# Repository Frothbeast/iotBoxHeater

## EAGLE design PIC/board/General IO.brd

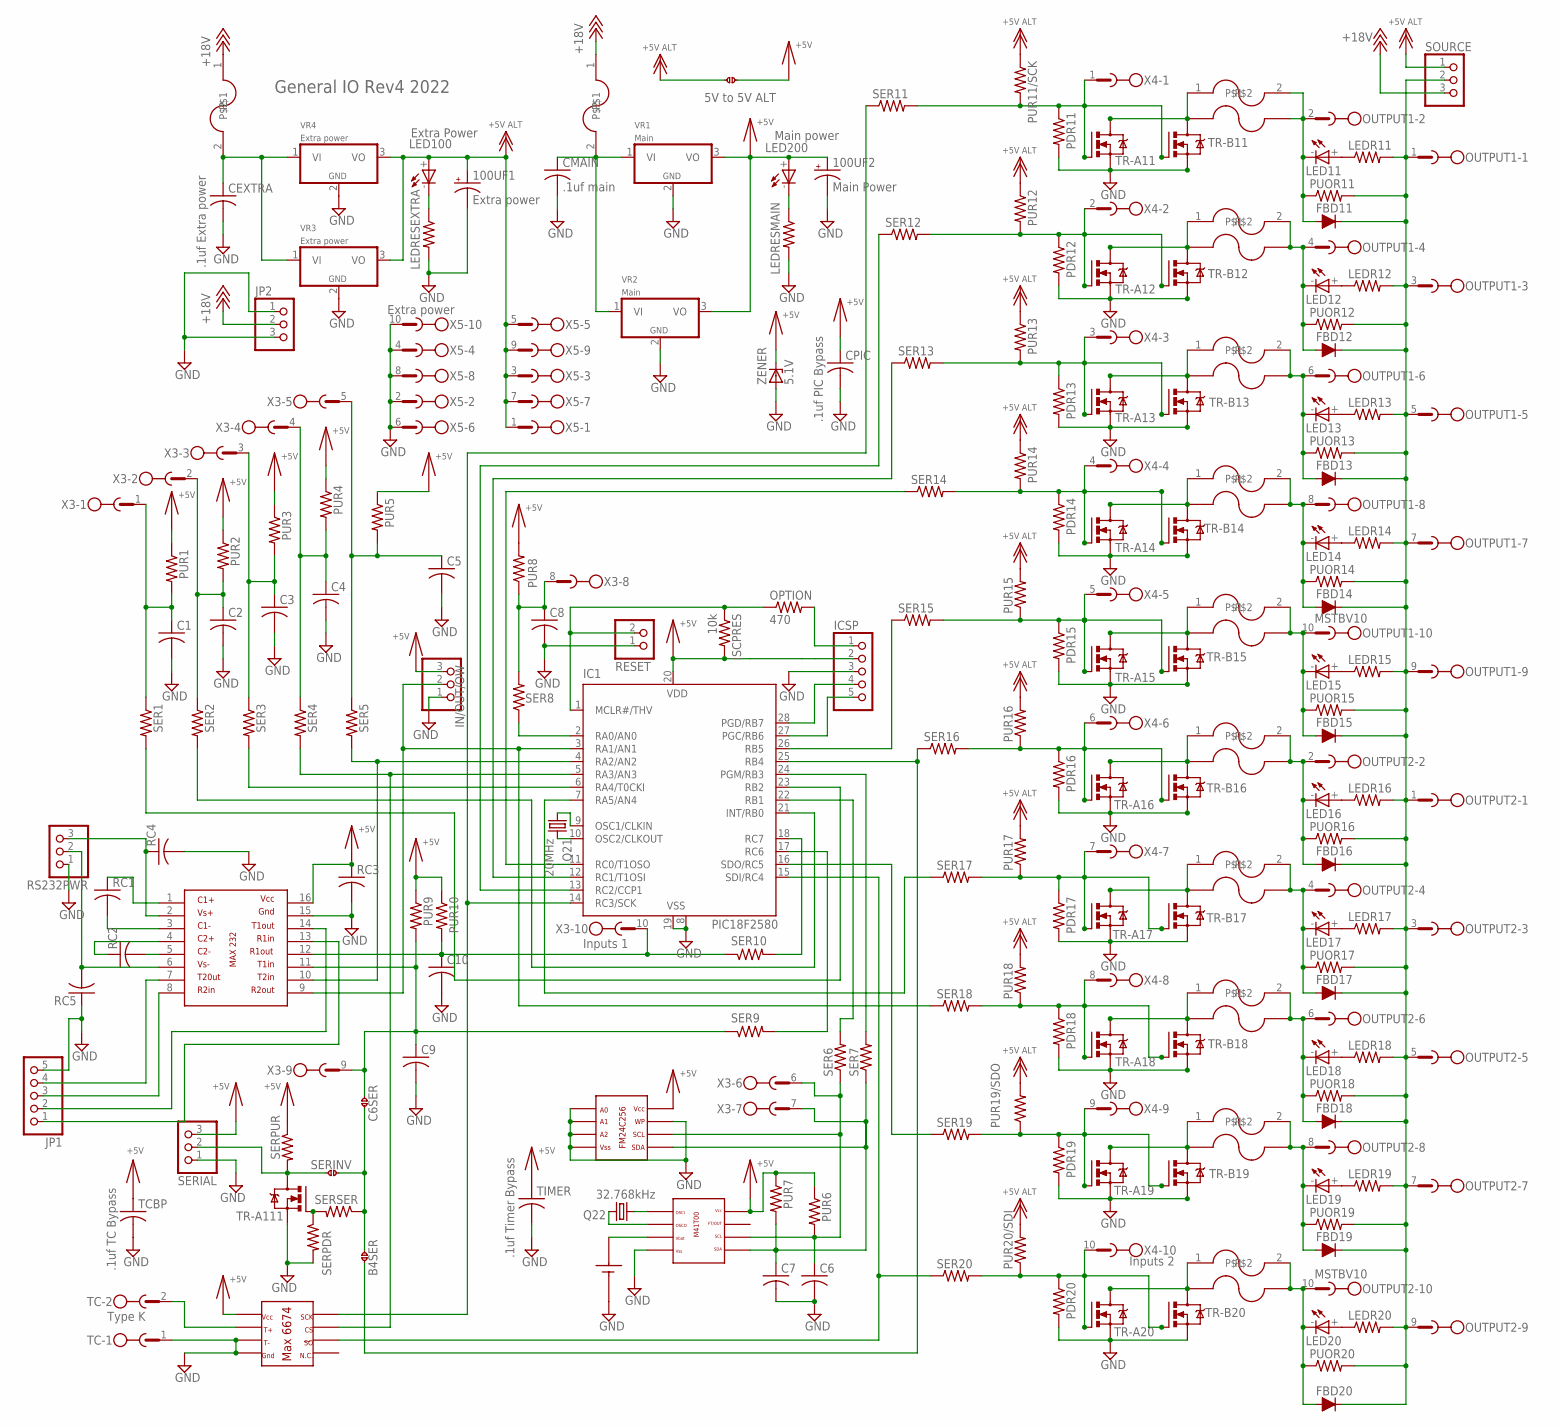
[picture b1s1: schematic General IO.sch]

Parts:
100UF1: Extra power; PANASONIC_G
100UF2: Main Power; PANASONIC_G
BAT1: BH-401
C1, C2, C3, C4, C5, C6, C7, C8, C9, C10: CAPACITOR-NO-POLARITYC1210; C1210
C6SER: SPLIT_PAD
CEXTRA: .1uf Extra power; C1210
CMAIN: .1uf main; C1210
CPIC: .1uf PIC Bypass; C1210
FBD11, FBD12, FBD13, FBD14, FBD15, FBD16, FBD17, FBD18, FBD19, FBD20: D-FILL-SOD-87; SOD87
FUSE9, FUSE11, FUSE12, FUSE13, FUSE14, FUSE15, FUSE16, FUSE17, FUSE18, FUSE20: FUSE(SM); FUSE
IC1: PIC18F2580; SO-28W
ICSP: PINHD-1X5; 1X05
IN/OUT/OW: PINHD-1X3; 1X03
ISCPRES: 10k; M1406
JP1: PINHD-1X5; 1X05
JP2: PINHD-1X3; 1X03
LED11, LED12, LED13, LED14, LED15, LED16, LED17, LED18, LED19, LED20: LED; 1206
LED100: Extra Power; 1206
LED200: Main power; 1206
LEDR11, LEDR12, LEDR13, LEDR14, LEDR15, LEDR16, LEDR17, LEDR18, LEDR19, LEDR20: RESISITORM1406; M1406
LEDRESEXTRA: RESISITORR1210; R1210
LEDRESMAIN: RESISITORR1210; R1210
OPTION: 470; M1406
OUTPUT1, OUTPUT2: MSTBV10
PDR11, PDR12, PDR13, PDR14, PDR15, PDR16, PDR17, PDR18, PDR19, PDR20: RESISITORM1406; M1406
POLYFUSE11, POLYFUSE12, POLYFUSE13, POLYFUSE14, POLYFUSE15, POLYFUSE16, POLYFUSE17, POLYFUSE18, POLYFUSE19, POLYFUSE20: POLYFUSE; 0204/5
POLYFUSE100: Extra Power; 0204/5
POLYFUSE200: Main power; 0204/5
PUOR11, PUOR12, PUOR13, PUOR14, PUOR15, PUOR16, PUOR17, PUOR18, PUOR19, PUOR20: RESISITORM1406; M1406
PUR1, PUR2, PUR3, PUR4, PUR5, PUR6, PUR7, PUR8, PUR9, PUR10, PUR11/SCK, PUR12, PUR13, PUR14, PUR15, PUR16, PUR17, PUR18, PUR19/SDO, PUR20/SDI: RESISITORM1406; M1406
Q21: 20MHz; SM49
Q22: 32.768kHz; TC26H
RC1, RC2, RC3, RC4, RC5: CAPACITOR-NO-POLARITYC1210; C1210
RESET: PINHD-1X2; 1X02
RS232PWR: PINHD-1X3; 1X03
SER1, SER2, SER3, SER4, SER5, SER6, SER7, SER8, SER9, SER10, SER11, SER12, SER13, SER14, SER15, SER16, SER17, SER18, SER19, SER20: RESISITORM1406; M1406
SERIAL: PINHD-1X3; 1X03
SERPDR: RESISITORM1406; M1406
SERPUR: RESISITORM1406; M1406
SERSER: RESISITORM1406; M1406
SOURCE: PINHD-1X3; 1X03
TC: Type K; MSTBV2
TCBP: .1uf TC Bypass; C1210
TIMER: .1uf Timer Bypass; C1210
TR-A11, TR-A12, TR-A13, TR-A14, TR-A15, TR-A16, TR-A17, TR-A18, TR-A19, TR-A20, TR-A111: ZXMN10A08GSOT223; SOT223R_INFINEON
TR-B11, TR-B12, TR-B13, TR-B14, TR-B15, TR-B16, TR-B17, TR-B18, TR-B19, TR-B20: ZXMN10A08G; TO220BV
U$1: MAX232; SO16
U$2: MAX6674; SO08
U$4: M41T00TIMER-I2C; SO08
U$18: FM24C256; SO08
U$21, U$23, U$24: SPLIT_PAD
VR1: Main; TO220S
VR2: Main; SOT223R_INFINEON
VR3: Extra power; SOT223R_INFINEON
VR4: Extra power; TO220S
X3: Inputs 1; MSTBV10
X4: Inputs 2; MSTBV10
X5: Extra power; MSTBV10
ZENER: 5.1V; SMB

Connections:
$N199: IC1.15 (SDI/RC4), SER20.1, U$2.7
+5V: 100UF2.+, CPIC.1, IC1.20 (VDD), ICSP.2, IN/OUT/OW.3, ISCPRES.2, LED200.+, PUR1.1, PUR2.1, PUR3.1, PUR4.1, PUR5.1, PUR6.1, PUR7.1, PUR8.2, PUR9.1, PUR10.1, RC3.1, SERIAL.3, SERPUR.1, TCBP.1, TIMER.1, U$1.16, U$2.4, U$4.8 (VCC), U$18.8 (VDD), U$21.P$1, VR1.3 (VO), VR2.3 (VO), ZENER.C
+18V: JP2.2, POLYFUSE100.1, POLYFUSE200.1, SOURCE.3
ALT5V: 100UF1.+, LED100.+, PUR11/SCK.1, PUR12.1, PUR13.1, PUR14.1, PUR15.2, PUR16.2, PUR17.2, PUR18.2, PUR19/SDO.2, PUR20/SDI.2, SOURCE.1, U$21.P$2, VR3.3 (VO), VR4.3 (VO), X5.1, X5.3, X5.5, X5.7, X5.9
GND: 100UF1.-, 100UF2.-, BAT1.P$2, C1.2, C2.2, C3.2, C4.2, C5.2, C6.2, C7.2, C8.2, C9.2, C10.2, CEXTRA.2, CMAIN.2, CPIC.2, IC1.8 (VSS), IC1.19 (VSS), ICSP.3, IN/OUT/OW.1, JP1.5, JP2.1, JP2.3, LEDRESEXTRA.2, LEDRESMAIN.2, PDR11.2, PDR12.2, PDR13.2, PDR14.2, PDR15.2, PDR16.2, PDR17.2, PDR18.2, PDR19.2, PDR20.2, RC3.2, RC4.2, RC5.1, RESET.1, RS232PWR.1, SERIAL.1, SERPDR.2, TC.1, TCBP.2, TIMER.2, TR-A11.3 (S), TR-A12.3 (S), TR-A13.3 (S), TR-A14.3 (S), TR-A15.3 (S), TR-A16.3 (S), TR-A17.3 (S), TR-A18.3 (S), TR-A19.3 (S), TR-A20.3 (S), TR-A111.3 (S), TR-B11.S, TR-B12.S, TR-B13.S, TR-B14.S, TR-B15.S, TR-B16.S, TR-B17.S, TR-B18.S, TR-B19.S, TR-B20.S, U$1.15, U$2.1, U$2.2, U$4.4 (VSS), U$18.1 (A0), U$18.2 (A1), U$18.3 (A2), U$18.4 (VSS), U$18.7 (WP), VR1.2 (GND), VR2.2 (GND), VR3.2 (GND), VR4.2 (GND), X5.2, X5.4, X5.6, X5.8, X5.10, ZENER.A
unnamed: FUSE17.P$1, POLYFUSE17.1, TR-A17.2 (D), TR-B17.D
unnamed: FUSE9.P$1, POLYFUSE19.1, TR-A19.2 (D), TR-B19.D
unnamed: PDR18.1, PUR18.1, SER18.2, TR-A18.1 (G), TR-B18.G, X4.8
unnamed: FBD16.2 (A), FUSE16.P$2, LED16.-, OUTPUT2.2, POLYFUSE16.2, PUOR16.1
unnamed: FBD17.2 (A), FUSE17.P$2, LED17.-, OUTPUT2.4, POLYFUSE17.2, PUOR17.1
unnamed: FUSE16.P$1, POLYFUSE16.1, TR-A16.2 (D), TR-B16.D
unnamed: FUSE18.P$1, POLYFUSE18.1, TR-A18.2 (D), TR-B18.D
unnamed: IC1.7 (RA5/AN4), SER17.1
unnamed: FBD20.2 (A), FUSE20.P$2, LED20.-, OUTPUT2.10, POLYFUSE20.2, PUOR20.1
unnamed: FBD18.2 (A), FUSE18.P$2, LED18.-, OUTPUT2.6, POLYFUSE18.2, PUOR18.1
unnamed: IC1.16 (SDO/RC5), SER19.1
unnamed: IC1.2 (RA0/AN0), SER8.1
unnamed: FBD19.2 (A), FUSE9.P$2, LED19.-, OUTPUT2.8, POLYFUSE19.2, PUOR19.1
unnamed: FUSE20.P$1, POLYFUSE20.1, TR-A20.2 (D), TR-B20.D
unnamed: IC1.21 (INT/RB0), SER2.2
unnamed: FBD12.2 (A), FUSE12.P$2, LED12.-, OUTPUT1.4, POLYFUSE12.2, PUOR12.1
unnamed: FUSE15.P$1, POLYFUSE15.1, TR-A15.2 (D), TR-B15.D
unnamed: FBD15.2 (A), FUSE15.P$2, LED15.-, OUTPUT1.10, POLYFUSE15.2, PUOR15.1
unnamed: JP1.4, U$1.7
unnamed: PDR17.1, PUR17.1, SER17.2, TR-A17.1 (G), TR-B17.G, X4.7
unnamed: FUSE14.P$1, POLYFUSE14.1, TR-A14.2 (D), TR-B14.D
unnamed: FBD14.2 (A), FUSE14.P$2, LED14.-, OUTPUT1.8, POLYFUSE14.2, PUOR14.1
unnamed: FUSE13.P$1, POLYFUSE13.1, TR-A13.2 (D), TR-B13.D
unnamed: FBD13.2 (A), FUSE13.P$2, LED13.-, OUTPUT1.6, POLYFUSE13.2, PUOR13.1
unnamed: PDR15.1, PUR15.1, SER15.2, TR-A15.1 (G), TR-B15.G, X4.5
unnamed: PDR13.1, PUR13.2, SER13.2, TR-A13.1 (G), TR-B13.G, X4.3
unnamed: FUSE12.P$1, POLYFUSE12.1, TR-A12.2 (D), TR-B12.D
unnamed: PDR14.1, PUR14.2, SER14.2, TR-A14.1 (G), TR-B14.G, X4.4
unnamed: FUSE11.P$1, POLYFUSE11.1, TR-A11.2 (D), TR-B11.D
unnamed: FBD11.2 (A), FUSE11.P$2, LED11.-, OUTPUT1.2, POLYFUSE11.2, PUOR11.1
unnamed: IC1.28 (PGD/RB7), ICSP.4
unnamed: PDR16.1, PUR16.1, SER16.2, TR-A16.1 (G), TR-B16.G, X4.6
unnamed: IC1.23 (RB2), SER1.2
unnamed: ICSP.1, OPTION.2
unnamed: IC1.10 (OSC2/CLKOUT), Q21.2
unnamed: SERPDR.1, SERSER.2, TR-A111.1 (G)
unnamed: IC1.1 (MCLR#/THV), ISCPRES.1, OPTION.1, RESET.2
unnamed: SERIAL.2, SERPUR.2, TR-A111.2 (D), U$23.P$1
unnamed: IC1.9 (OSC1/CLKIN), Q21.1
unnamed: IC1.27 (PGC/RB6), ICSP.5
unnamed: C10.1, PUR10.2, SER10.1, U$1.12, X3.10
unnamed: IC1.4 (RA2/AN2), SER5.2, U$1.10
unnamed: C6SER.P$1, C9.1, PUR9.2, SER9.1, U$1.11, X3.9
unnamed: JP1.3, U$1.8
unnamed: TC.2, U$2.3
unnamed: CEXTRA.1, POLYFUSE100.2, VR3.1 (VI), VR4.1 (VI)
unnamed: C2.1, PUR2.2, SER2.1, X3.2
unnamed: JP1.2, U$1.14
unnamed: C4.1, PUR4.2, SER4.1, X3.4
unnamed: FBD11.1 (C), FBD12.1 (C), FBD13.1 (C), FBD14.1 (C), FBD15.1 (C), FBD16.1 (C), FBD17.1 (C), FBD18.1 (C), FBD19.1 (C), FBD20.1 (C), LEDR11.2, LEDR12.2, LEDR13.2, LEDR14.2, LEDR15.2, LEDR16.2, LEDR17.2, LEDR18.2, LEDR19.2, LEDR20.2, OUTPUT1.1, OUTPUT1.3, OUTPUT1.5, OUTPUT1.7, OUTPUT1.9, OUTPUT2.1, OUTPUT2.3, OUTPUT2.5, OUTPUT2.7, OUTPUT2.9, PUOR11.2, PUOR12.2, PUOR13.2, PUOR14.2, PUOR15.2, PUOR16.2, PUOR17.2, PUOR18.2, PUOR19.2, PUOR20.2, SOURCE.2
unnamed: Q22.1, U$4.2 (OSCO)
unnamed: Q22.2, U$4.1 (OSCI)
unnamed: LED200.-, LEDRESMAIN.1
unnamed: BAT1.P$1, U$4.3 (VBAT)
unnamed: IC1.22 (RB1), SER6.2
unnamed: PDR11.1, PUR11/SCK.2, SER11.2, TR-A11.1 (G), TR-B11.G, X4.1
unnamed: IC1.24 (PGM/RB3), SER7.2
unnamed: JP1.1, U$1.13
unnamed: C8.1, PUR8.1, SER8.2, X3.8
unnamed: IC1.18 (RC7), SER10.2
unnamed: CMAIN.1, POLYFUSE200.2, VR1.1 (VI), VR2.1 (VI)
unnamed: LED20.+, LEDR20.1
unnamed: LED19.+, LEDR19.1
unnamed: LED100.-, LEDRESEXTRA.1
unnamed: LED18.+, LEDR18.1
unnamed: IC1.17 (RC6), SER9.2
unnamed: LED17.+, LEDR17.1
unnamed: LED16.+, LEDR16.1
unnamed: LED15.+, LEDR15.1
unnamed: LED14.+, LEDR14.1
unnamed: LED13.+, LEDR13.1
unnamed: LED12.+, LEDR12.1
unnamed: LED11.+, LEDR11.1
unnamed: PDR12.1, PUR12.2, SER12.2, TR-A12.1 (G), TR-B12.G, X4.2
unnamed: C3.1, PUR3.2, SER3.1, X3.3
unnamed: PDR19.1, PUR19/SDO.1, SER19.2, TR-A19.1 (G), TR-B19.G, X4.9
unnamed: PDR20.1, PUR20/SDI.1, SER20.2, TR-A20.1 (G), TR-B20.G, X4.10
unnamed: RC2.2, U$1.5
unnamed: RC1.2, U$1.3
unnamed: RC2.1, U$1.4
unnamed: RC1.1, U$1.1
unnamed: RC4.1, RS232PWR.3, U$1.2
unnamed: RC5.2, RS232PWR.2, U$1.6
unnamed: C5.1, PUR5.2, SER5.1, X3.5
unnamed: C1.1, PUR1.2, SER1.1, X3.1
unnamed: IC1.14 (RC3/SCK), SER11.1, U$2.5
unnamed: IC1.13 (RC2/CCP1), SER12.1
unnamed: IC1.12 (RC1/T1OSI), SER13.1
unnamed: IC1.5 (RA3/AN3), SER4.2, U$2.6
unnamed: IC1.6 (RA4/T0CKI), SER3.2
unnamed: IC1.11 (RC0/T1OSO), SER14.1
unnamed: IC1.25 (RB4), SER16.1, U$24.P$2
unnamed: IC1.26 (RB5), SER15.1
unnamed: C6SER.P$2, SERSER.1, U$23.P$2, U$24.P$1
unnamed: C6.1, PUR6.2, SER6.1, U$4.6 (SCL), U$18.6 (SCL), X3.6
unnamed: C7.1, PUR7.2, SER7.1, U$4.5 (SDA), U$18.5 (SDA), X3.7
SER18: IC1.3 (RA1/AN1), IN/OUT/OW.2, SER18.1, U$1.9

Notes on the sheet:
General IO Rev4 2022
C6SER
B4SER
SERINV
5V to 5V ALT

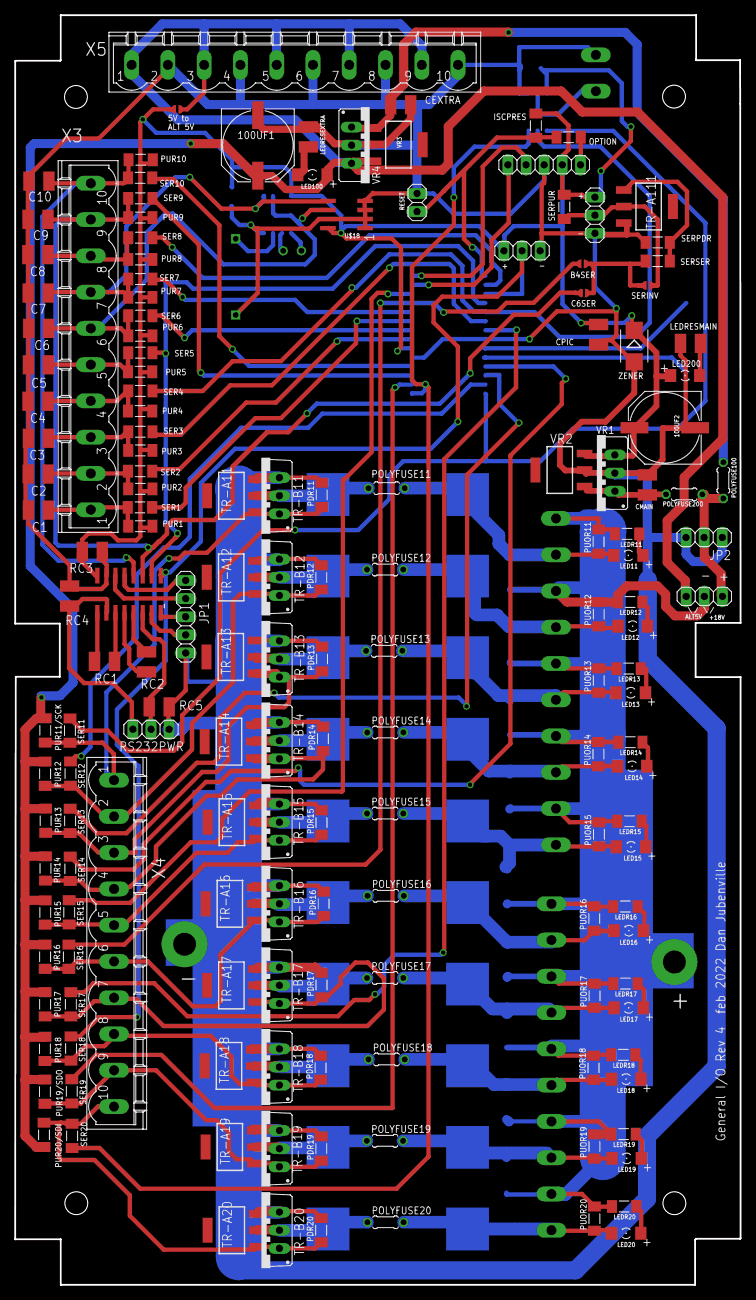
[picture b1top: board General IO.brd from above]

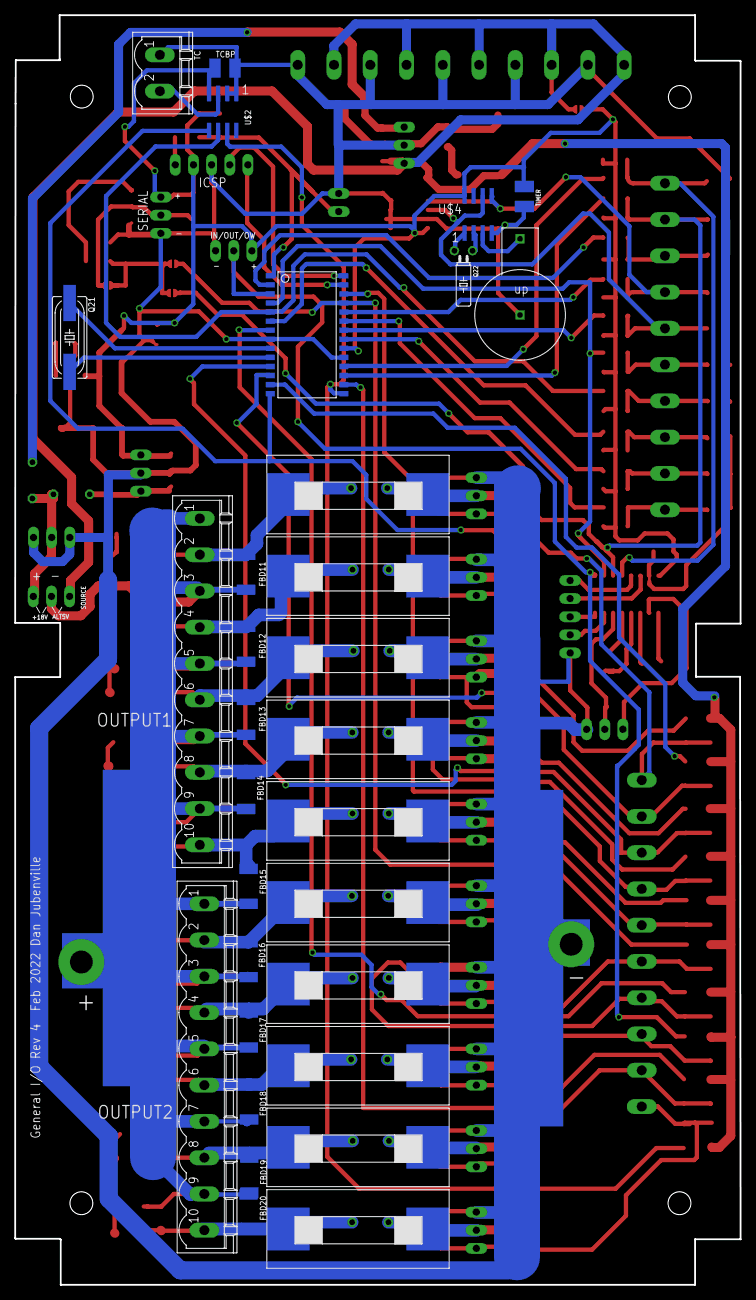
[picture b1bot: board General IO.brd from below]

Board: 2 copper layers, 101.6 x 177.8 mm, 199 parts (31 on the bottom side), 102 nets.

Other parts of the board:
U$11, U$13, U$14, U$15: SCREW

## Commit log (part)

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2026-01-12 changes to add more to the list.
2026-03-29 added cad to project
2026-04-05 rearranged to PIC folder
2026-04-05 initial setup of pic portion of repository Signed-off-by: Frothbeast <frothbeast@gmail.com>
2026-04-14 Maybe switching to ESP only, but PIC is better is power is not an issue
2026-04-15 esp will look for ip or host a site to set new ip
2026-04-15 goo start to the ESP32 holder for the same dish as ESP-01s
2026-04-15 created holder and slide
2026-04-17 Attempted to guess proper tolerances for 3D printing this to work with original dish
2026-04-17 updated program and BOM to get ready to build the board
2026-04-17 changed BOM to match reality(I hope)
2026-04-20 copied a bunch of files from the greenhouse folder like Doug Scott would
2026-04-20 copied poorly the grrnhouse client Signed-off-by: Frothbeast <frothbeast@gmail.com>
2026-04-20 removed improper dockerfile
2026-04-20 Heater not Greenhouse
2026-04-20 added sunlight and changed temp to box and heater
2026-04-20 changed folder name to add Box
2026-04-20 changed folder name to add Box again
2026-04-20 more conversion from greenhouse to heater, but needs more work
2026-04-20 updated a lot to match database and get frompic to esp to database
2026-04-21 aligned client with server
2026-04-22 added route to index
2026-04-22 added route to time Signed-off-by: Frothbeast <frothbeast@gmail.com>
